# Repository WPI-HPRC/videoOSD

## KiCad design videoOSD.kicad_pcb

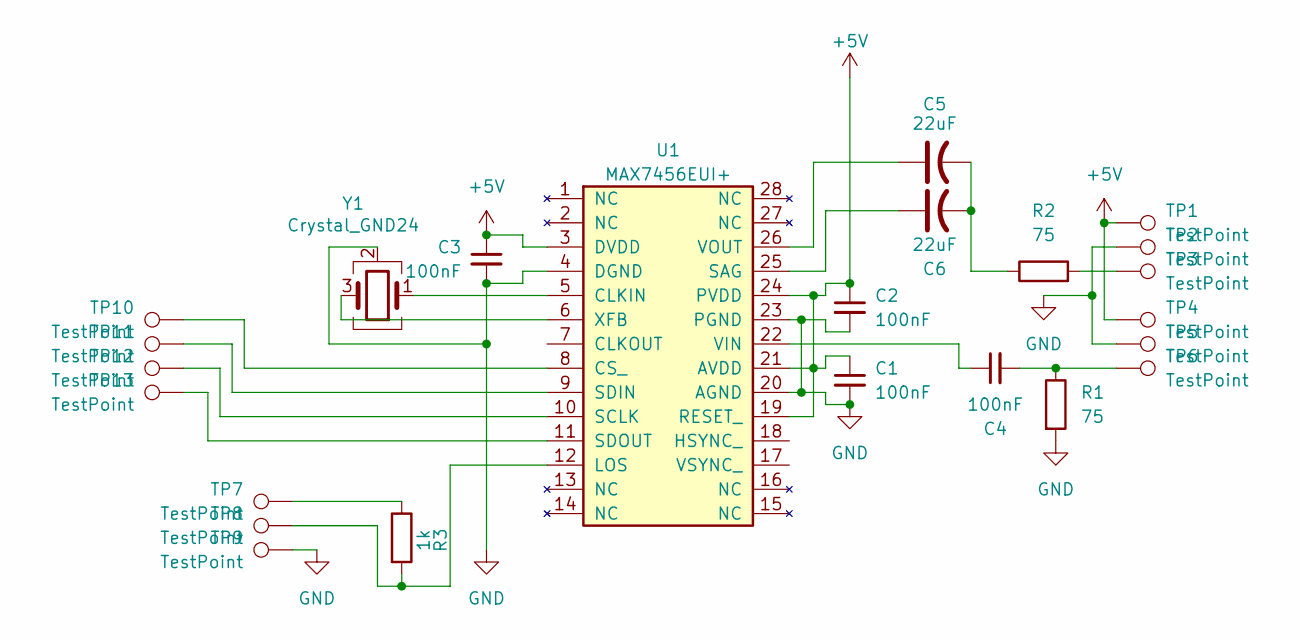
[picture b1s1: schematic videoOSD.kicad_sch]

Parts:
C1, C2, C3, C4: 100nF; C_0402_1005Metric
C5, C6: 22uF; C_0603_1608Metric
R1, R2: 75; R_0402_1005Metric
R3: 1k; R_0402_1005Metric
TP1, TP2, TP3, TP4, TP5, TP6, TP7, TP8, TP9: TestPoint; TestPoint_THTPad_1.0x1.0mm_Drill0.5mm
TP10, TP11, TP12, TP13: TestPoint; TestPoint_Pad_1.0x1.0mm
U1: MAX7456EUI+; TSSOP-28_4.4x9.7mm_P0.65mm
Y1: Crystal_GND24; Crystal_SMD_3225-4Pin_3.2x2.5mm

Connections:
+5V: C1.1, C2.1, C3.1, TP1.1, TP4.1, U1.3 (DVDD), U1.19 (RESET_), U1.21 (AVDD), U1.24 (PVDD)
GND: C1.2, C2.2, C3.2, R1.2, TP2.1, TP5.1, TP9.1, U1.4 (DGND), U1.20 (AGND), U1.23 (PGND), Y1.2 (G), Y1.4 (G)
unnamed: C4.2, R1.1, TP6.1
unnamed: C5.2, C6.2, R2.1
unnamed: R2.2, TP3.1
unnamed: R3.1, TP7.1
unnamed: U1.5 (CLKIN), Y1.1
unnamed: TP10.1, U1.8 (CS_)
unnamed: R3.2, TP8.1, U1.12 (LOS)
unnamed: C6.1, U1.25 (SAG)
unnamed: TP12.1, U1.10 (SCLK)
unnamed: TP11.1, U1.9 (SDIN)
unnamed: TP13.1, U1.11 (SDOUT)
unnamed: C4.1, U1.22 (VIN)
unnamed: C5.1, U1.26 (VOUT)
unnamed: U1.6 (XFB), Y1.3

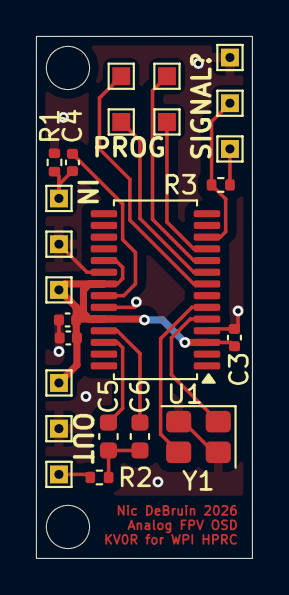
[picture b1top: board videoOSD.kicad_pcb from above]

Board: 2 copper layers, 12.0 x 29.0 mm, 24 parts (0 on the bottom side), 16 nets.

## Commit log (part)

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2026-02-01 done
2026-02-27 pcb done
2026-03-07 initial code commit
2026-05-20 configuration is done, now need to write actual characters
2026-05-20 add gitignore
2026-06-09 welp?
2026-06-09 i need to break out a logic analyzer... this will be a during hockey event
2026-06-10 it works now. horray
2026-06-10 works fr
2026-06-10 put it more in the corner
2026-06-15 screw it, just add a teensy to the bay lol
